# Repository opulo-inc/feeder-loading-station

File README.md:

# Feeder Loading Station

The Feeder Loading Station is an accessory used to help load electronic component tape into LumenPnP Feeders.

The FLS is effectively a short length of extrusion with a powered slot, used to provide a dedicated station to power the feeder while loading in component tape. It accepts a standard 24v barrel jack (same as what's used with the LumenPnP) and provides power to the single slot on the rail.

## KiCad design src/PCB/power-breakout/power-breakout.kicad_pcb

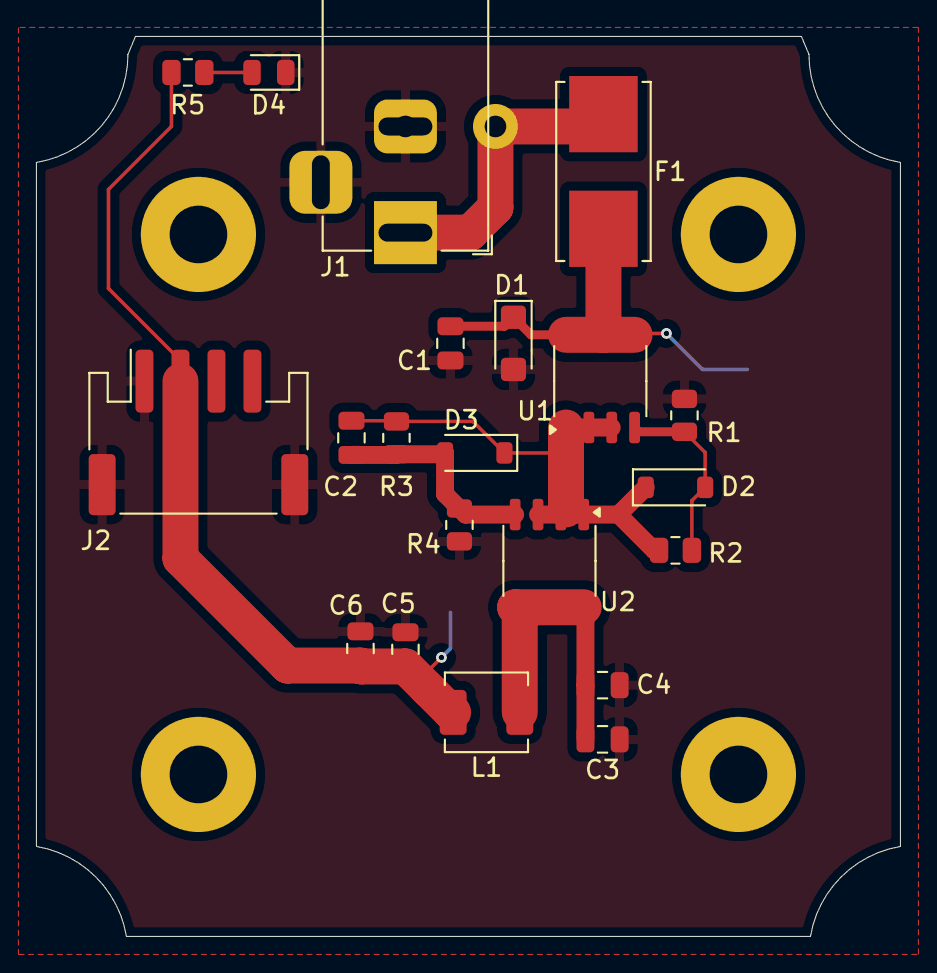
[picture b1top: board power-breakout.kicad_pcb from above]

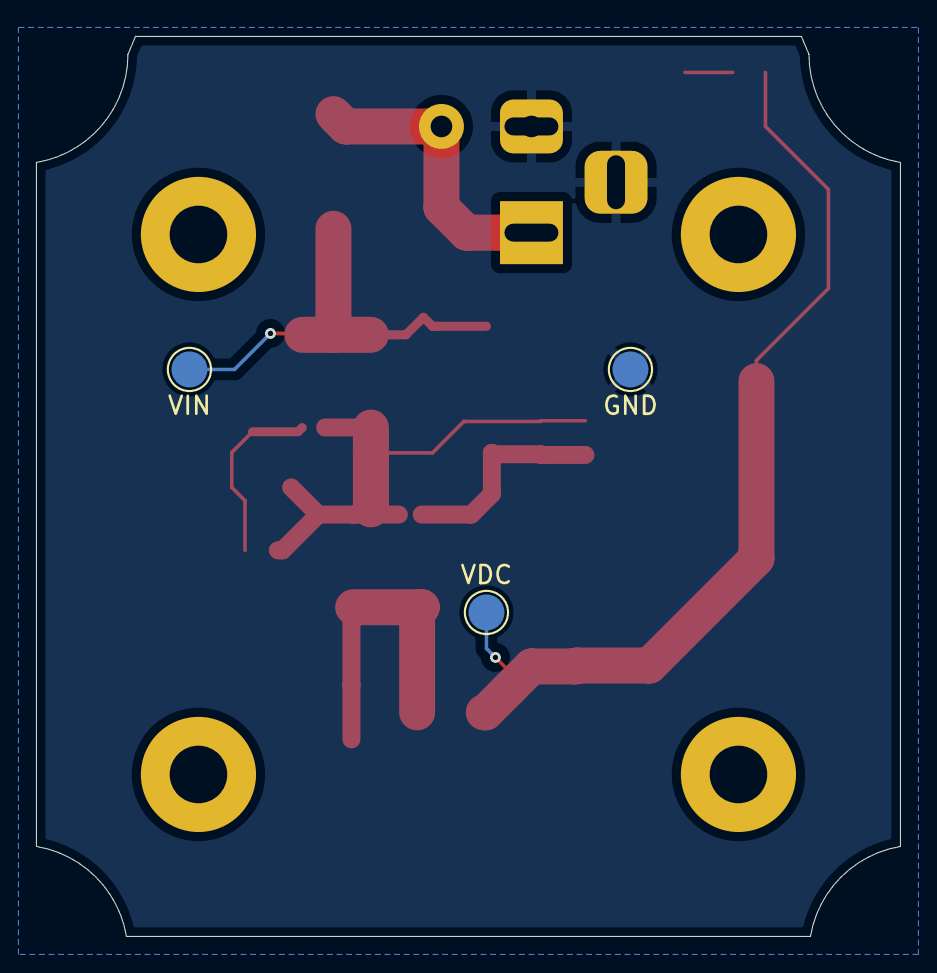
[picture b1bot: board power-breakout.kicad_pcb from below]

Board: 2 copper layers, 48.0 x 50.0 mm, 24 parts (3 on the bottom side), 9 nets.

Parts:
C1, C3, C4, C5, C6: 10u; C_0805_2012Metric
C2: 100n; C_0805_2012Metric
D1: SMF28A; D_SMF
D2, D3: BZT52C16; D_SOD-123
D4: Green; LED_0805_2012Metric
F1: Fuse; Fuseholder_Littelfuse_Nano2_154x
GND: TestPoint; TestPoint_Pad_D2.0mm
J1: COMBO_POWER_JACK; BarrelJack_Horizontal
J2: Conn_01x04_Pin; JST_PH_S4B-PH-SM4-TB_1x04-1MP_P2.00mm_Horizontal
L1: 2.2u; L_Sunlord_MWSA0402S
R1, R4, R5: 10k; R_0805_2012Metric
R2, R3: 4.7k; R_0805_2012Metric
U1, U2: FDS4435BZ; SO-8_3.9x4.9mm_P1.27mm
VDC: TestPoint; TestPoint_Pad_D2.0mm
VIN: TestPoint; TestPoint_Pad_D2.0mm

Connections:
/POWER_SUPPLY: F1.1, J1.1, J1.4
/VIN: C1.2, D1.1 (A1), F1.2, U1.5 (D), U1.6 (D), U1.7 (D), U1.8 (D), VIN.1
GND: C1.1, C3.1, C4.1, C5.1, C6.1, D1.2 (A2), D4.1 (K), GND.1, J1.2, J1.3, J2.1, J2.MP, R1.2, R4.2
unnamed: C3.2, C4.2, L1.1, U2.5 (D), U2.6 (D), U2.7 (D), U2.8 (D)
unnamed: D2.2 (A), R1.1, R2.2, U1.4 (G)
unnamed: C2.2, D2.1 (K), D3.1 (K), R2.1, R3.1, U1.1 (S), U1.2 (S), U1.3 (S), U2.1 (S), U2.2 (S), U2.3 (S)
unnamed: C2.1, D3.2 (A), R3.2, R4.1, U2.4 (G)
unnamed: D4.2 (A), R5.2
VDC: C5.2, C6.2, J2.2, L1.2, R5.1, VDC.1

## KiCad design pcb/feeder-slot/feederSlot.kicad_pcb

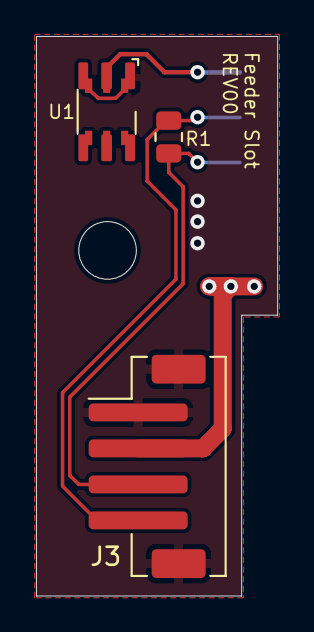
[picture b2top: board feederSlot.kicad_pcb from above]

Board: 2 copper layers, 13.4 x 31.1 mm, 5 parts (1 on the bottom side), 5 nets.

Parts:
H1: MountingHole; MountingHole_3.2mm_M3
J2: Conn_01x05_Female; AVX-915-005-541-Contact-Surface
J3: Conn_01x04_Pin; JST_PH_B4B-PH-SM4-TB_1x04-1MP_P2.00mm_Vertical
R1: 120R; R_0805_2012Metric
U1: DS28E07; DS28E07_MULTI

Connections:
1WIRE: J2.1, U1.2 (IO)
GND: J2.4, J3.1, J3.MP, U1.1 (GND)
RS-485+: J2.2, J3.4, R1.2
RS-485-: J2.3, J3.3, R1.1
VIN: J2.5, J3.2

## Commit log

2026-02-03 updates gitignore
2026-02-03 updates .gitignore
2026-02-03 updates base to have corrected cable channel, reorgs files
2026-02-03 updates cable length to the correct 300mm
2026-02-03 updates asm, adds proper self-tapping screw
2026-02-18 updates part source for breakout, updates silkscreen
2026-02-20 renames photon-harness
2026-02-23 updates placement for silk on feeder-slot
2026-03-20 cleanup
2026-03-20 adds slot pcb, updates asm, updates slot bracket
2026-04-29 updates slot bracket
2026-05-16 opens up slot for extrusion a bit for an easier fit, adds icon, adds recesses for rubber feet alignment
2026-05-27 this commit represents PVT-01
2026-05-27 release prep
2026-06-05 cleans up assembly
